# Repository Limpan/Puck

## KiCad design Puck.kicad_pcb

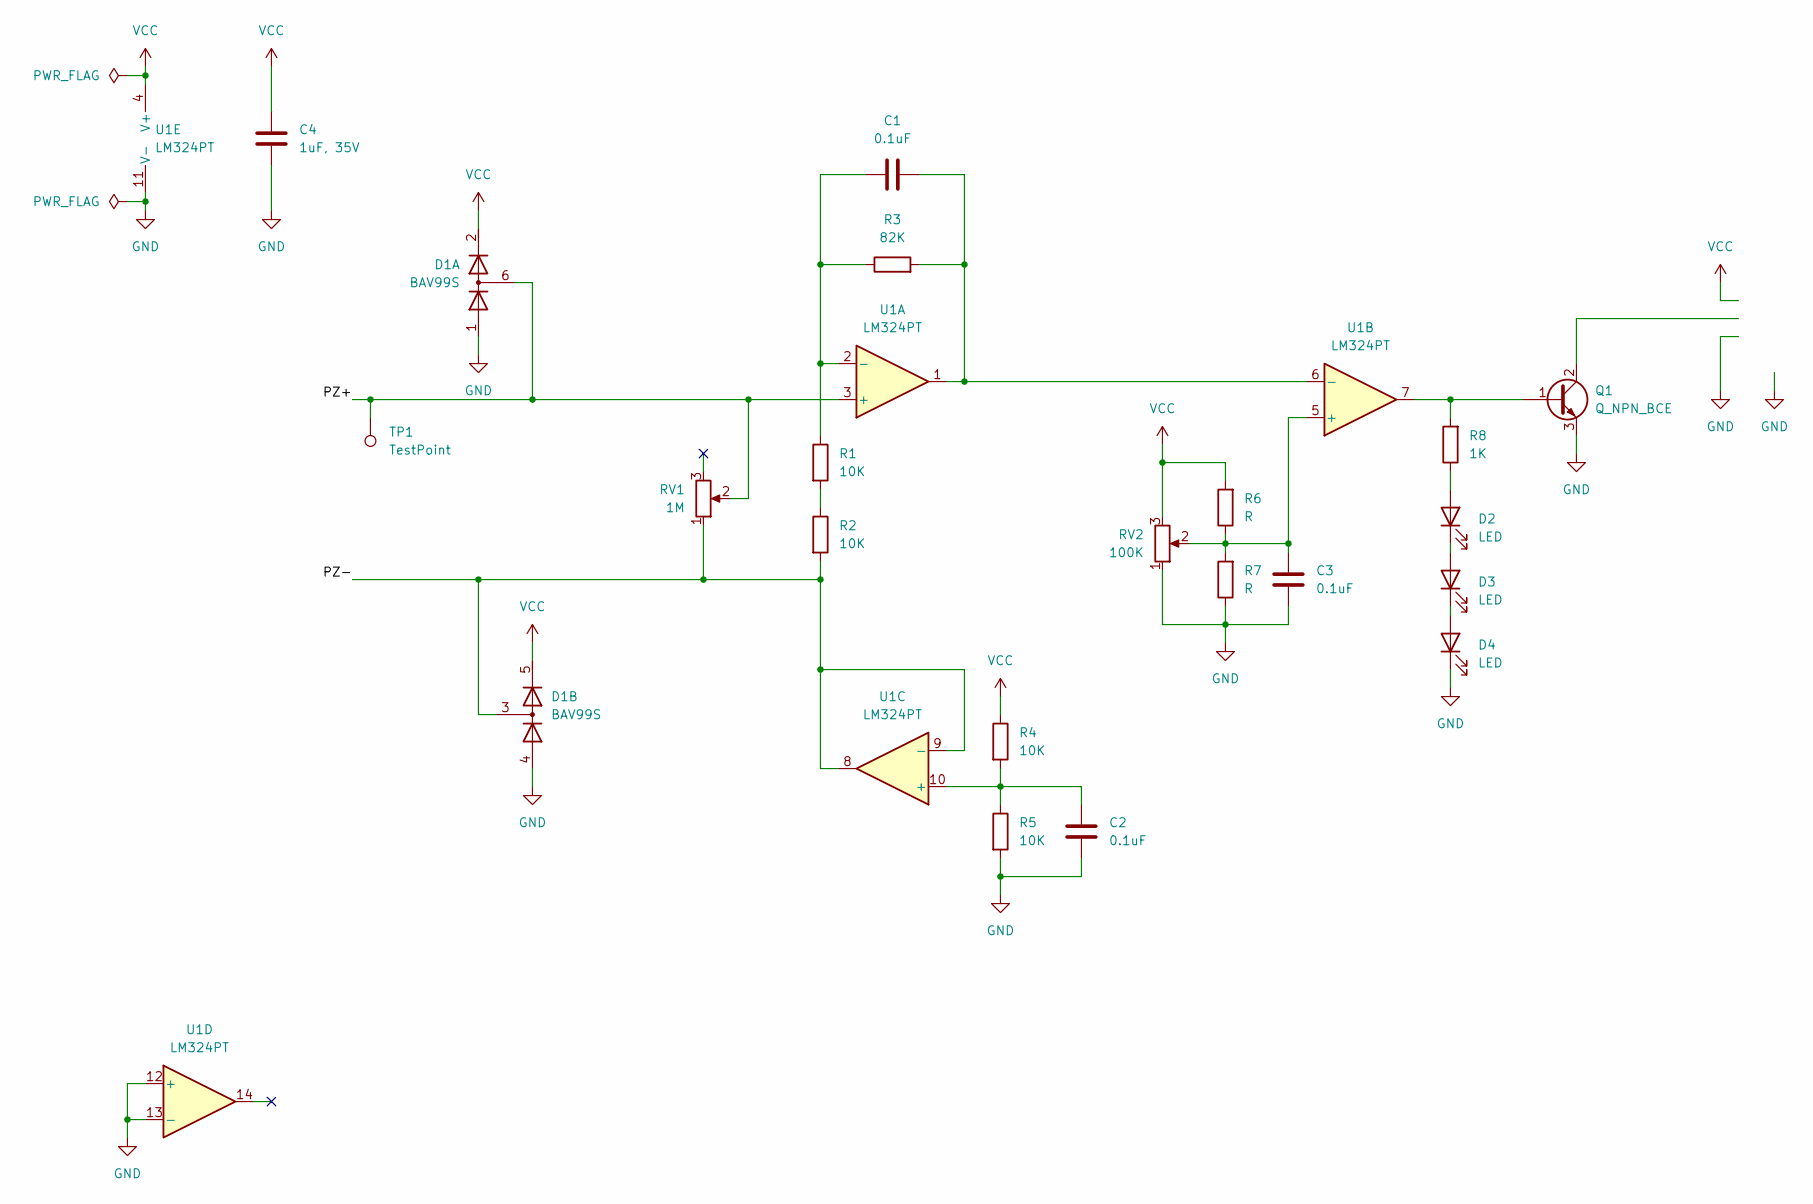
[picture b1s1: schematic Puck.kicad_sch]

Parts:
C1, C2, C3: 0.1uF; C_0603_1608Metric_Pad1.08x0.95mm_HandSolder
C4: 1uF, 35V; C_0603_1608Metric_Pad1.08x0.95mm_HandSolder
D1: BAV99S; SOT-363_SC-70-6
D2, D3, D4: LED; LED_0603_1608Metric_Pad1.05x0.95mm_HandSolder
Q1: Q_NPN_BCE; SOT-23
R1, R2, R4, R5: 10K; R_0603_1608Metric_Pad0.98x0.95mm_HandSolder
R3: 82K; R_0603_1608Metric_Pad0.98x0.95mm_HandSolder
R6, R7: R; R_0603_1608Metric_Pad0.98x0.95mm_HandSolder
R8: 1K; R_0603_1608Metric_Pad0.98x0.95mm_HandSolder
RV1: 1M; Potentiometer_Bourns_3314J_Vertical
RV2: 100K; Potentiometer_Bourns_3314J_Vertical
TP1: TestPoint; TestPoint_Pad_2.0x2.0mm
U1: LM324PT; TSSOP-14_4.4x5mm_P0.65mm

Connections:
/PZ+: D1.6 (K3A4), RV1.2, TP1.1, U1.3 (+)
/PZ-: D1.3 (K1A2), R2.2, RV1.1, U1.8, U1.9 (-)
GND: C2.2, C3.1, C4.1, D1.1 (A1), D1.4 (A3), D4.1 (K), Q1.3 (E), R5.2, R7.1, RV2.1, U1.11 (V-), U1.12 (+), U1.13 (-); also elsewhere on the board
unnamed: C1.1, R1.1, R3.1, U1.2 (-)
unnamed: C1.2, R3.2, U1.1, U1.6 (-)
unnamed: C2.1, R4.2, R5.1, U1.10 (+)
unnamed: C3.2, R6.1, R7.2, RV2.2, U1.5 (+)
unnamed: D2.1 (K), D3.2 (A)
unnamed: D2.2 (A), R8.1
unnamed: D3.1 (K), D4.2 (A)
unnamed: Q1.1 (B), R8.2, U1.7
unnamed 11: Q1.2 (C); also elsewhere on the board
unnamed: R1.2, R2.1
VCC: C4.2, D1.2 (K2), D1.5 (K4), R4.1, R6.2, RV2.3, U1.4 (V+); also elsewhere on the board

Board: 2 copper layers, 22 parts (0 on the bottom side), 14 nets, no tracks yet.

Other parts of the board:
J1: Conn_01x03; JST_PH_S3B-PH-SM4-TB_1x03-1MP_P2.00mm_Horizontal

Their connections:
GND: J1.3, J1.MP (MountPin); also elsewhere on the board
unnamed 11: J1.2; also elsewhere on the board
VCC: J1.1; also elsewhere on the board

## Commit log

2022-05-05 Initial work on schematic.
